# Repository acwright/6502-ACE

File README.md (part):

6502-ACE
========

An **AC6502** retro-style 8-bit computer based on the **65C02** microprocessor.

> 📖 **Guide:** [AC6502 Documentation](https://acwright.github.io/6502-DOCS/) — the user's and programmer's guide for the whole family.
> Start with [Your ACE](https://acwright.github.io/6502-DOCS/your-ace), the tour of this board.

---

**Building one? Every part you need, with supplier numbers and known issues, is in [BOM.md](BOM.md).**

## Table of Contents

- [Overview](#overview)
- [Architecture](#architecture)
- [Systems](#systems)
- [Software](#software)
- [Hardware](#hardware)
  - [ACE Board](#ace-board)
    - [The RTC](#the-rtc)
    - [Known limits](#known-limits)
  - [ACE CF Adapter](#ace-cf-adapter)
  - [ACE RAM Patch](#ace-ram-patch)
- [Which revision to make](#which-revision-to-make)
- [Works with the stock BIOS](#works-with-the-stock-bios)
- [Firmware](#firmware)
  - [Video card](#video-card)
  - [AB Controller](#ab-controller)
  - [ASDA Controller](#asda-controller)
- [CAD](#cad)
- [Production](#production)
- [Schematics](#schematics)
- [Shared lines](#shared-lines)
- [Extra pins: `EXP0`–`EXP3` and `HRDB`](#extra-pins-exp0exp3-and-hrdb)
- [Jumpers](#jumpers)
- [Off-board headers](#off-board-headers)
- [Docs](#docs)
- [Checking the schematics](#checking-the-schematics)
- [Checking the banked RAM](#checking-the-banked-ram)
- [Libraries](#libraries)
- [Bill of Materials](#bill-of-materials)
- [License](#license)

---

## Overview

The AC6502 ecosystem is a family of open-source, 65C02-based computers sharing a common architecture, memory map, and [BIOS](https://github.com/acwright/6502-BIOS). Each computer in the family is purpose-built for a different use case but runs the same software and firmware.

The **ACE** (All-in-one Computer Experience) is a complete, self-contained 65C02 computer on a single PCB. It integrates everything found across the COB's modular cards — CPU, memory, video, audio, storage, serial, GPIO, RTC, and keyboard controller — onto one board, delivering the full experience without a backplane or expansion cards.

## Architecture

All AC6502 computers share:

- **CPU**: 65C02 (or accurate emulation)
- **Memory**: 32KB RAM + 32KB ROM, with optional banked RAM expansion
- **Memory Map**: Standardized across the ecosystem — zero page, stack, I/O space ($8000–$9FFF), system ROM, and interrupt vectors at $FFFA–$FFFF
- **Bus**: 16-bit address bus, 8-bit bidirectional data bus, standard 65C02 control signals (RW, PHI2, RESET, IRQ, NMI, RDY, SYNC)
- **BIOS**: A common [BIOS](https://github.com/acwright/6502-BIOS) provides the kernel, monitor, and BASIC interpreter across all systems

## Systems

| Project | Description |
|---------|-------------|
| [6502-ACE](https://github.com/acwright/6502-ACE) | All-in-one Computer Experience — A single board computer (YOU ARE HERE) |
| [6502-COB](https://github.com/acwright/6502-COB) | Computer On a Backplane — Modular desktop computer with expandable card slots |
| [6502-DEV](https://github.com/acwright/6502-DEV) | Development Environment Vehicle — Emulation-based dev system |
| [6502-KIM](https://github.com/acwright/6502-KIM) | Keypad Input Monitor - KIM-1 inspired minimal computer |
| [6502-VCS](https://github.com/acwright/6502-VCS) | Video Computer System — Cartridge-based retro gaming console |

## Software

| Project | Description |
|---------|-------------|
| [6502-BIOS](https://github.com/acwright/6502-BIOS) | The shared BIOS (kernel, monitor, BASIC) for all AC6502 computers |
| [6502-PICOVDP](https://github.com/acwright/6502-PICOVDP) | Firmware for the ACE's video card, on a PICO9918 PRO v2.0 |
| [6502-EMULATOR](https://github.com/acwright/6502-EMULATOR) | Emulator for the whole family — desktop app, browser build, and a command line for scripted runs |
| [6502-PRG](https://github.com/acwright/6502-PRG) | Template project for writing assembly language programs |
| [6502-CRT](https://github.com/acwright/6502-CRT) | Template project for writing assembly language cartridges |
| [6502-ASM](https://github.com/acwright/6502-ASM) | Assembly language example programs and demos |
| [6502-BAS](https://github.com/acwright/6502-BAS) | BASIC program listings |
| [6502-WOZMON](https://github.com/acwright/6502-WOZMON) | Wozmon as a standalone ROM |
| [6502-NOP](https://github.com/acwright/6502-NOP) | An all-NOP ROM, for probing a board during bring-up |
| [6502-DOCS](https://github.com/acwright/6502-DOCS) | The documentation site — the guide, the printable reference cards, branding and label artwork |
| [cffs](https://github.com/acwright/cffs) | Builds CompactFlash disk images for the BIOS filesystem |
| [bastok](https://github.com/acwright/bastok) | Tokenizes BASIC listings into `.prg` images, and back |
| [bin2woz](https://github.com/acwright/bin2woz) | Converts a binary into a Wozmon serial upload |

## Hardware

This repository contains KiCad 7.0+ PCB designs for the ACE board.

### ACE Board
`Hardware/ACE Board/`

The single integrated board hosting the W65C02S CPU and all peripherals. Provides:

- **CPU**: W65C02S running at 1 MHz
- **RAM**: 32KB SRAM (62256) + Optional 512K banked SRAM (AS6C4008)
- **ROM**: 32KB EEPROM (28C256)
- **Video**: PICO9918 PRO v2.0 running [6502-PICOVDP](https://github.com/acwright/6502-PICOVDP) (VGA 640×480); see [Video card](#video-card). The silkscreen and the BOM's value field say `Pico9918A`
- **Audio**: ARMSID SID chip emulator (3-voice synthesis, RCA output)
- **Storage**: Storage adapter socket
- **Serial**: R6551AP ACIA with MAX238 level shifter (RS-232 via DB9, 50–19200 baud). Male DB-9 wired
  as **DTE**, like a PC, so reaching a laptop needs a **null-modem** cable. `RTS`, `DTR` and `DSR`
  always reach the cable; the `CTS EN` and `DCD EN` jumpers (J2 and J4) pick ground or the cable for
  those two inputs — **both default to ground**
- **GPIO**: 65C22 VIA (20 GPIO pins, 2× 16-bit timers, shift register)
- **RTC**: DS1511Y real-time clock with battery-backed NVRAM. Any revision also takes the RTC Adapter, and Rev 1.1 a DS1501; see [The RTC](#the-rtc)
- **Keyboard Controller**: ATmega1284 running AB Controller firmware
- **Input**: PS/2 keyboard connector and 8×8 keyboard matrix header
- **Joystick**: Two Atari 2600-compatible joystick ports (JOYSTICK A on VIA PORT A and JOYSTICK B on VIA PORT B, `J6` and `J8`), read as `JOY(2)` and `JOY(1)` respectively
- **Clock**: 16 MHz DIP-14 full can oscillator (X1); drives the ATmega1284 at 16 MHz and, through the 74HC163 divider (U5), the 65C02, VIA, ACIA and SID at 1 MHz, the speed every AC6502 is tested at. The PHI2 SELECT jumper (J1) offers 2 MHz on pins 2 and 3.
  - **Rev 1.0: keep J1 on 1 MHz** (pins 1 and 2). Its SID is clocked from the 1 MHz output whatever J1 says, so at 2 MHz it answers only every other CPU cycle.
  - **Rev 1.1: 2 MHz is an option at the builder's risk.** The CPU, VIA, ACIA and SID all follow J1. The limit the 2 MHz tests found, on 2026-11-11, is the RAM at U7: an Alliance AS6C62256 there misread at 2 MHz with one lot of 74HC00 at U14, the gate that makes `RB` and `WB`, and the Hitachi HM62256LP-70 read clean with the same 74HC00. The parts list orders the Hitachi for both revisions (2026-11-28), with a 74HC00 at U14. The cause of the Alliance's misreads isn't known. A made Rev 1.0 with an Alliance can misread at 1 MHz too: see the RAM row in [BOM.md's Known issues](BOM.md#known-issues). The R6551AP is rated for 2 MHz, with no margin, and read back clean at that speed. BIOS 2.1.0 finds the CompactFlash card at boot at 2 MHz, and reads and writes it clean there (tested on Rev 1.0 with the 74HCT00 at U14, 2026-11-12); BIOS 2.0.x misses the card at boot at 2 MHz.

**The serial handshake jumpers.** `CTS EN` and `DCD EN` (J2 and J4) both default to **ground**, and
that is how the boards were built. Ground means the line is permanently asserted, so the ACIA can
always send and always receive. Moved to the cable, they do real work — measured on a real R6551 in
2026: `CTS` high stops the transmitter dead and `DCD` high stops the receiver, losing the byte that
arrives. A board jumpered to the cable and plugged into something that does not assert those lines
shows no banner and no echo at all, and looks broken when it is not.
- **Reset**: Manual reset button (SW70, just above <kbd>Esc</kbd>) connected to the ATmega1284, which also provides power-on reset to the 65C02
- **Power**: 5V DC via barrel jack, center-positive only. The jack goes straight to the power switch, so `VCC` gets the full 5 V, and nothing protects the board from a reversed supply

**Cards on `CART` and `BUS`.** `IRQB`, `NMIB` and `RESB` are shared by several devices on the board and by
anything plugged into `CART` and `BUS` (J17 and J18). A card may only pull
those lines low, open-drain, and must never drive them high: a device that drives a shared line high holds it
there against every other device that pulls it low. A video card built around a pico9918 has the same `/INT`
problem as U3, and needs the same diode on the card.

#### The RTC

U18 is the real-time clock, with 256 bytes of battery-backed NVRAM. The DS1511Y is a DS1501 with its 32.768 kHz
crystal and a lithium cell built into one module: the same registers and pinout, so the BIOS runs either. The
[RTC Adapter](https://github.com/acwright/6502-COB#adapters), in 6502-COB, is a DS1501 and its crystal on a plug that fits any revision's socket, for less. Rev 1.1
also puts the crystal on the board (`Y2`), so its socket takes the bare chip too:

| Rev | DS1511Y | RTC Adapter | DS1501 (DIP) |
|---|---|---|---|
| 1.0 | Yes, the part it was made and tested with | Yes, untested | No: it has no crystal |
| 1.1 | Yes | Yes, untested | Yes, untested |

With the RTC Adapter or a DS1501:
- **Keep the CR2032 fitted** (`BT1`). It is the DS1501's only backup, so taking it out loses the time and the NVRAM.
  A DS1511Y has its own cell as well.
- **Use BIOS 1.8 or 2.2.0 or later.** A new DS1501 may start with its Crystal Select bit set, and then it runs slow
  on the 6 pF crystal; the BIOS clears the bit at every boot from those releases on
  ([6502-BIOS #4](https://github.com/acwright/6502-BIOS/issues/4)).
- **The DS1501YN+, the DIP chip, is not for new designs** (NRND). Digi-Key lists it (2026-11-20); Mouser doesn't. The
  RTC Adapter's DS1501YZN+, in SOIC, is active.

#### Known limits

- **The SID probe:** BIOS 2.0.x missed the SID (an ARMSID) at 1 MHz about once in a dozen boots, because it read voice 3 only once. BIOS 2.1.0 reads it several times: on 2026-11-12 it found the ARMSID on 10 boots of 10, and with IO7 switched off on IO ENABLE (SW69) found no SID on 10 of 10. Use 2.1.0 or later.
- **The CompactFlash probe:** BIOS 2.0.x waited for the card with a loop counted in CPU cycles, about 851 ms at 1 MHz and half that at 2 MHz, so a slow card could be missed. BIOS 2.1.0 passes over an empty slot at once and otherwise waits up to 3.0 s at 1 MHz (1.5 s at 2 MHz). A Promaster 128 MB card is ready in about 434 ms.

### ACE CF Adapter
`Hardware/ACE CF Adapter/`

A CompactFlash adapter board that connects to the Storage header on the ACE Board. Provides:

- **Interface**: 8-bit IDE (True IDE) mode
- **Storage**: CompactFlash socket. The BIOS filesystem divides the card into 256 disk banks of 1 MB each, so 256 MB is the usable capacity regardless of the card fitted
- **Revisions**: Rev 1.0 is the board on sale, and its silkscreen says `J21` for STORAGE and `J3` for the CF socket. See the [revision history](REVISIONS.md#ace-cf-adapter)

### ACE RAM Patch
`Hardware/ACE RAM Patch/`

A patch board for Rev 1.0 of the ACE Board that corrects the extended RAM (banked SRAM) decoding, with the same logic as Rev 1.1. U12 and U13 come off the ACE, chips and sockets, and the patch is soldered underneath in their place. Provides:

- **Fix**: `LOADL` and `LOADH` go high only on a write to the bank register, `$83FF` or `$87FF`, while PHI2 is high. Rev 1.0 pulsed both latches whenever the bus was idle, and the first patch (Rev 1.0) fixed that but still loaded a latch on any write to `$8300`–`$83FE` and `$80FF`–`$82FF` (and the same in the `$8400` window)
- **Interface**: two DIP-14 footprints of pin headers, J1 into U12's holes and J2 into U13's, soldered on both boards. The patch mounts front side up under the ACE, so its layout is not mirrored; U13's pin 1 is 23.00 mm from U12's pin 1 along the row
- **Layout**: U1, J1, J2 and U2 in one row, 92.6 × 13.1 mm. J1 and J2 are on the front, facing the ACE; U1 (74HC00) and U2 (74HC02) are on the back, hanging below, so trim their leads flush on the front. The patch hangs about 8.5 mm below the ACE: the header, the board, and the chips
- **Rev 1.1**: replaces the Rev 1.0 patch, which plugged into U13 alone
- **Status**: Rev 1.1 is verified on hardware. Its decode passes `Tests/check-schematics.mjs`, and on 2026-11-03 an ACE Board Rev 1.0 with the patch fitted passed `node Tests/check-ram.mjs --expect FF` with every card in place: `HW_PRESENT` read `$FF` after each of 10 restarts, each latch loaded only on its own address, and every bank of both windows held its own patterns, with 0 failures in 3 runs. The same board had 0 failures in 3 runs without the video card and the CF Adapter, reading `$77`. Without the patch, a Rev 1.0 reads `$FD`, because the BIOS doesn't find the `$8400` window. See [Checking the banked RAM](#checking-the-banked-ram)

<!-- Which revision to make: generated by Tools/revision-audit/register.py from Tools/data/orders.json. Edit that file, not this section. -->
## Which revision to make

**Make the newest revision of a board, and check its label first.** The table below gives each board's newest revision. A newer revision fixes what was found on the older ones. Every revision, old and new, is in [REVISIONS.md](REVISIONS.md), with what changed in each.

Each revision carries one of three labels:

- **Tested:** This revision was built and tested.
- **Proven design:** Not built at this revision, but its circuit is proven. Either it is a tested revision's circuit, or each change copies a circuit built and tested on another board or on the bench, or is a textbook circuit that leaves everything the tested revision does as it was. Any other change is silkscreen text, part values, mounting holes, outline clean-up, parts moved a fraction of a millimetre onto their grid, capacitor pitch, socket outlines, a footprint swap with the same holes, a solder jumper's default, the solder mask or paste at a card edge, or tracks rerouted or pours refilled with DRC and the netlist check passing. A builder can treat it as tested.
- **Untested:** The circuit, the power path or the layout changed in a way that only a built board proves, or the board has never been built at all.

[BOM.md](BOM.md) has the parts for every revision, and its known issues.

| Board | Newest revision | Label | Why |
|---|---|---|---|
| ACE Board | 1.1 | **Proven design** | Each change is a circuit already tested on a Rev 1.0: the ACE RAM Patch 1.1's bank-latch decode and the video card's `/INT` diode, both run on the bench, and the ACIA's crystal jumpers, which ship open. The audio jack's pins are put right, `SOB` is tied high, the pull-ups are 10k, and the tracks are rerouted, with the decode check passing. The DS1501 option at U18, with its crystal `Y2`, is untested, and so are the 10k pull-ups on the PS/2 lines, a textbook circuit. |
| ACE CF Adapter | 1.1 | **Proven design** | The same circuit as the tested Rev 1.0, renumbered and in surface-mount parts for JLCPCB assembly. The new LCSC socket fits the same footprint, but no board has been built with it yet. |
| ACE RAM Patch | 1.1 | **Tested** | Built and tested on an ACE Board Rev 1.0, 2026-11-03. |
| ACE SD Adapter Bottom | 1.1 | **Untested** | A new board: an SD card the stock BIOS takes for CompactFlash, with a built-in drive; the ACE SD Adapter Top, stacked on it, carries the SD card socket. Not yet made. |
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
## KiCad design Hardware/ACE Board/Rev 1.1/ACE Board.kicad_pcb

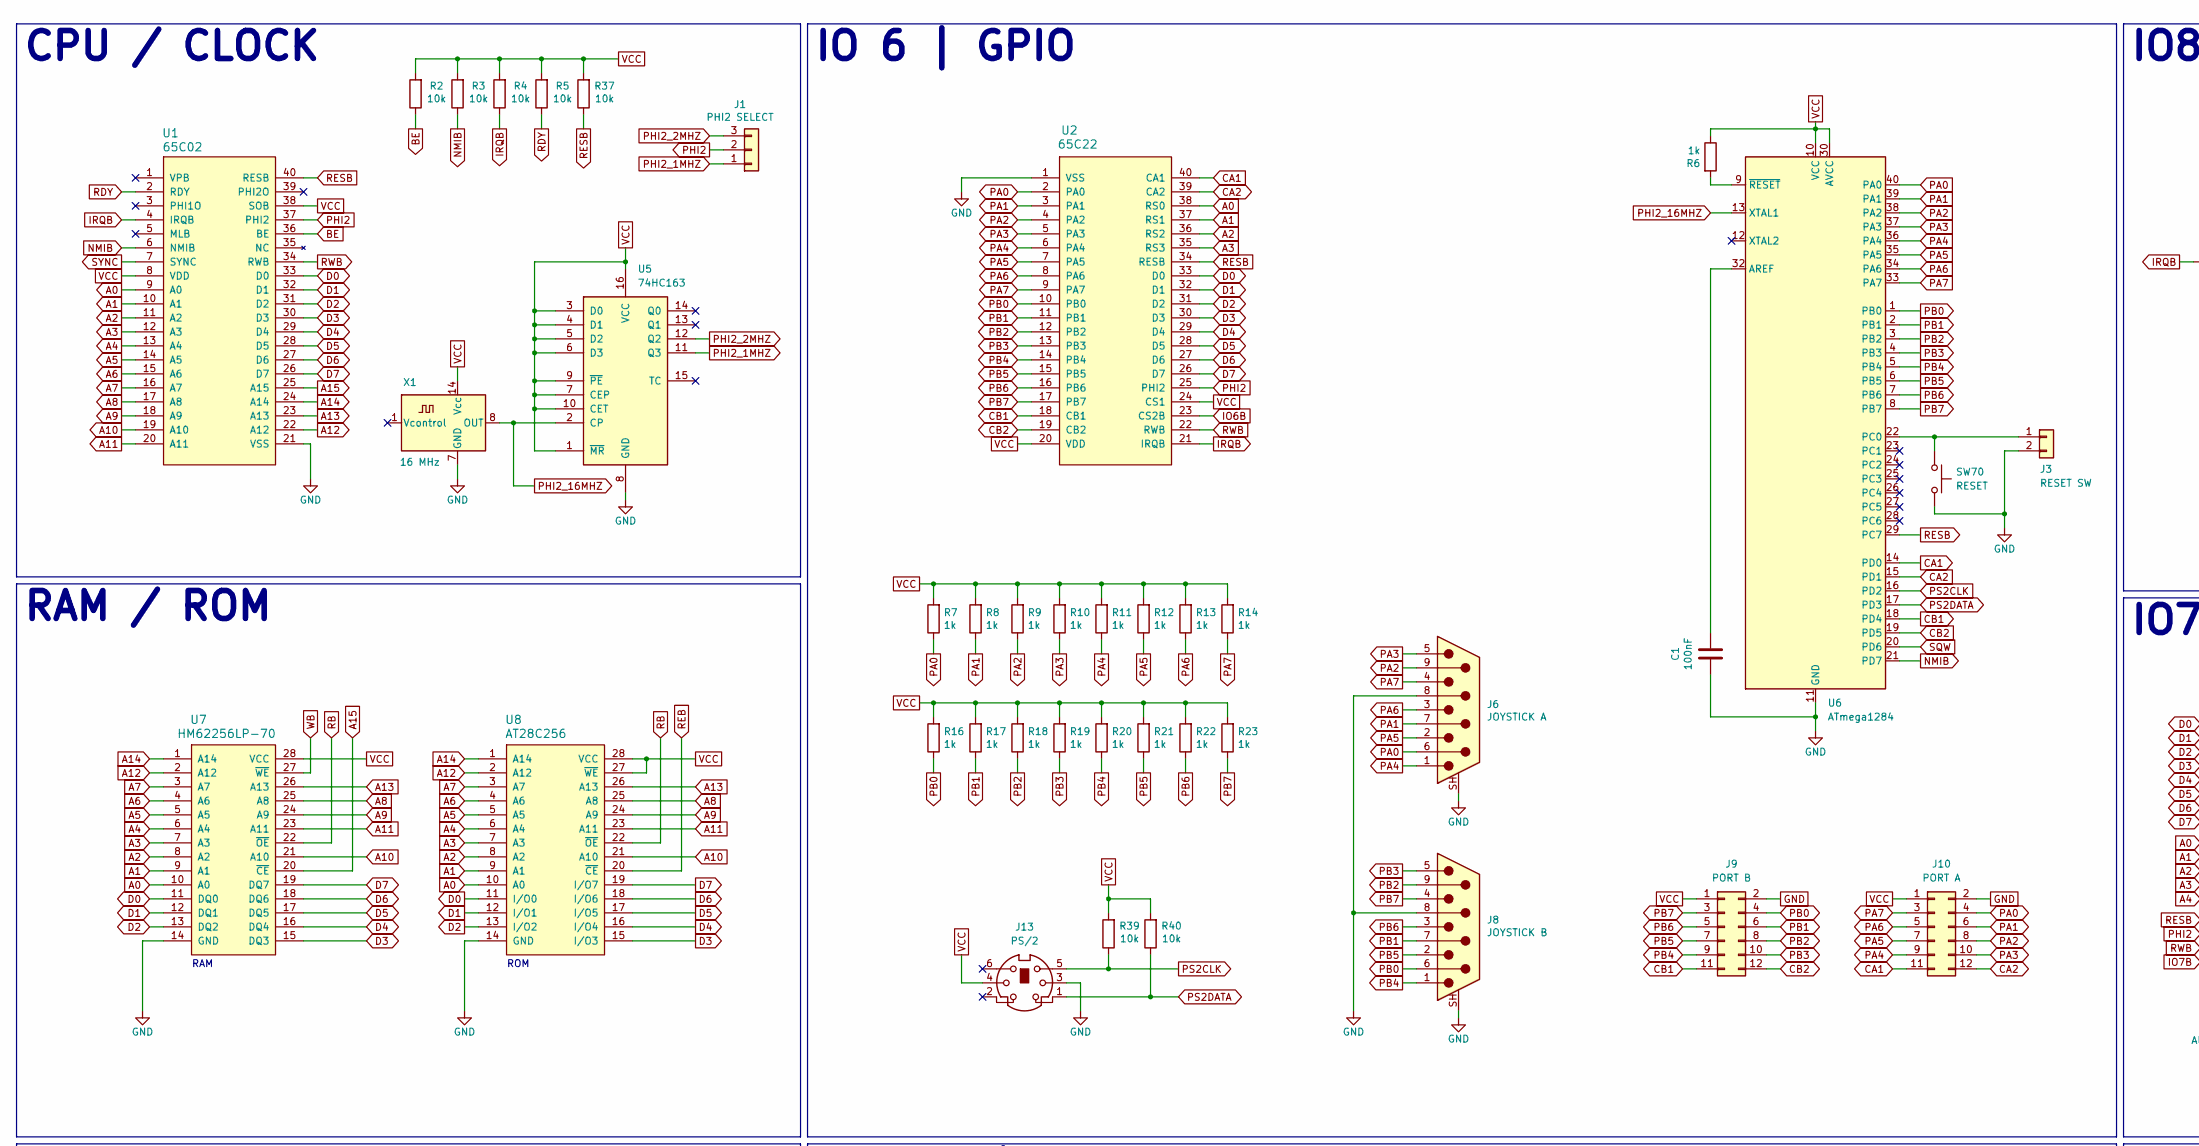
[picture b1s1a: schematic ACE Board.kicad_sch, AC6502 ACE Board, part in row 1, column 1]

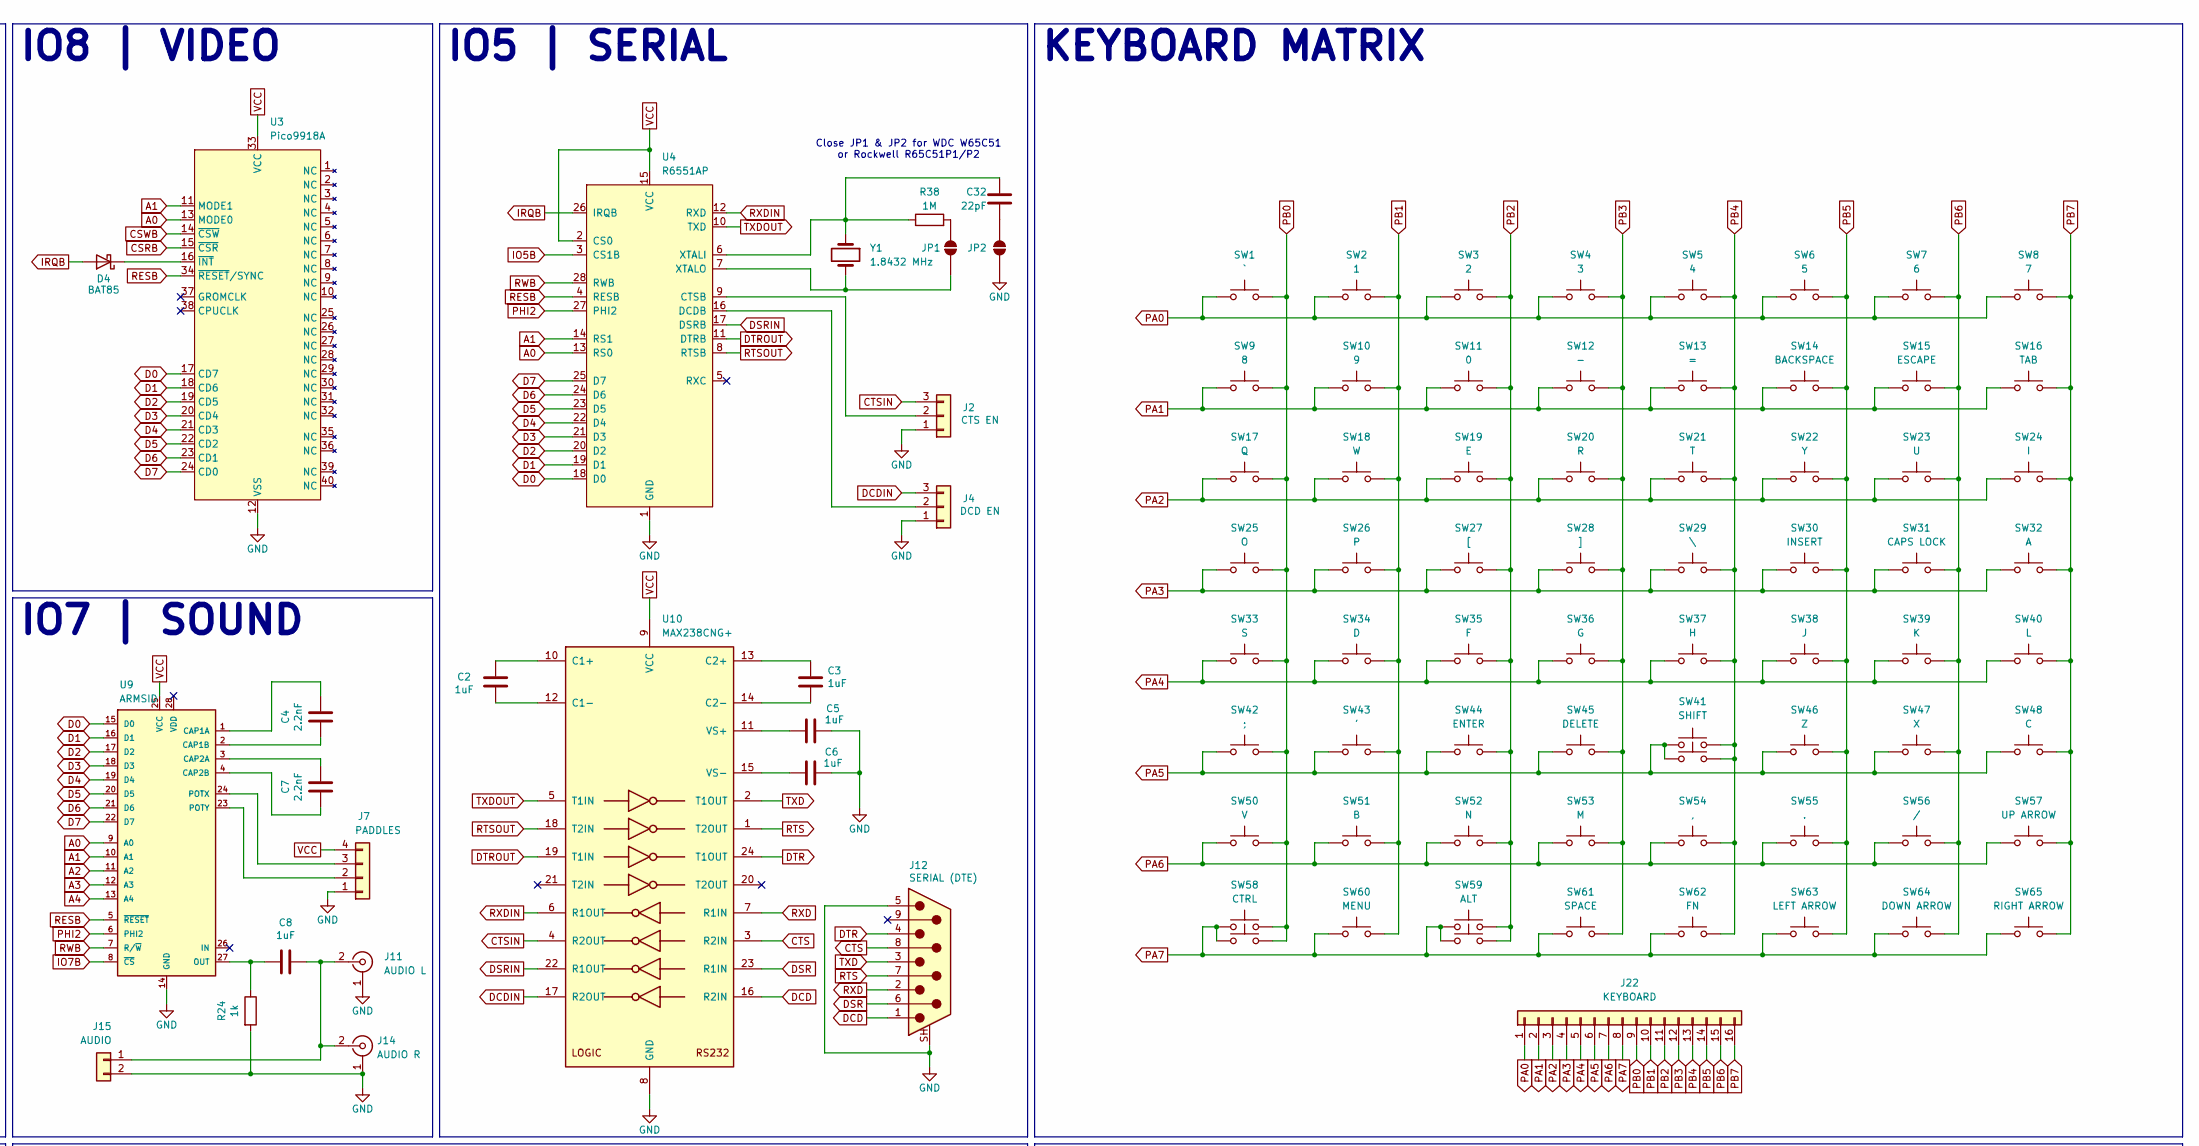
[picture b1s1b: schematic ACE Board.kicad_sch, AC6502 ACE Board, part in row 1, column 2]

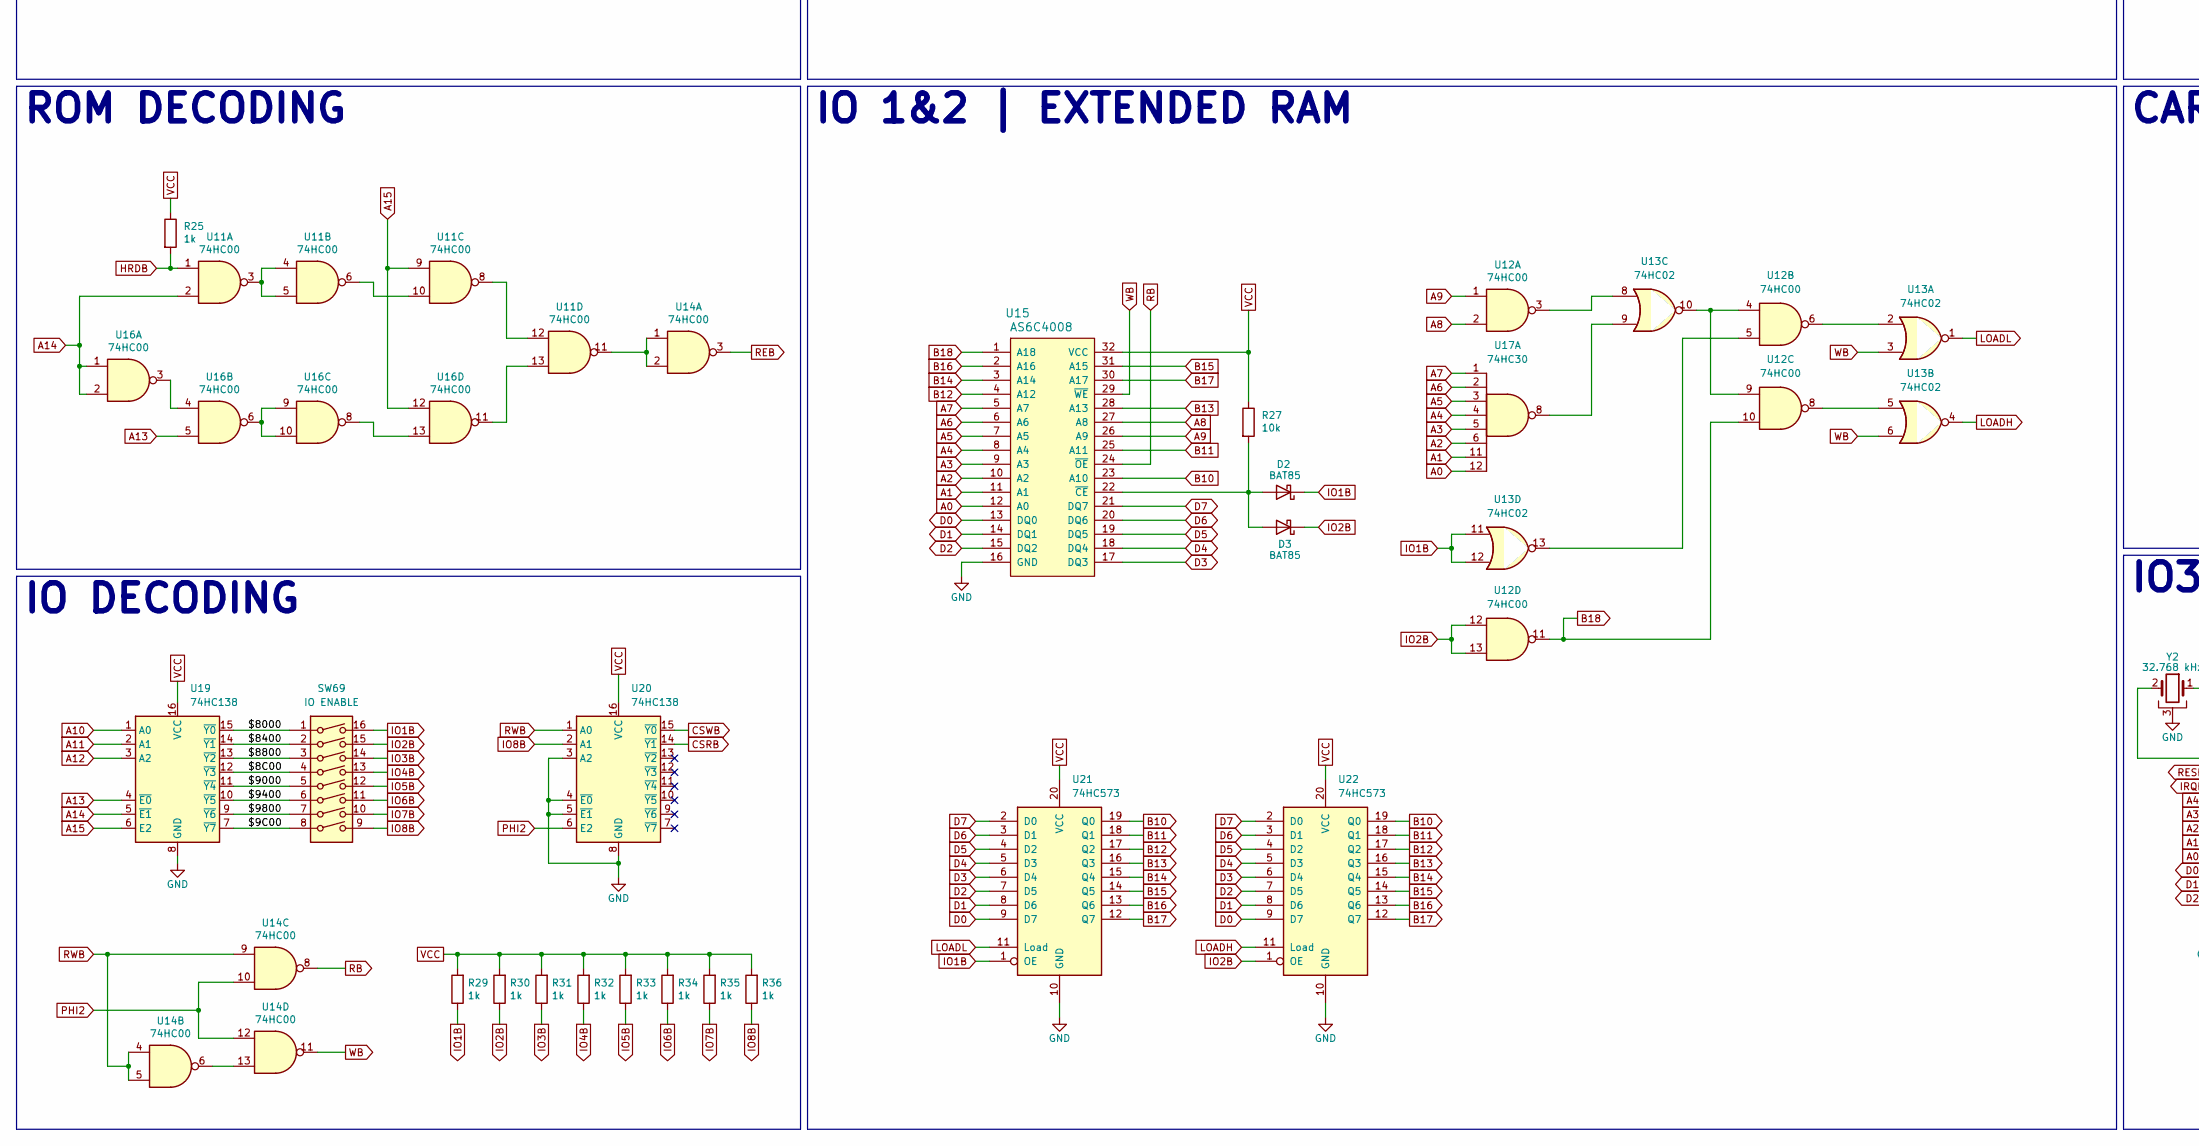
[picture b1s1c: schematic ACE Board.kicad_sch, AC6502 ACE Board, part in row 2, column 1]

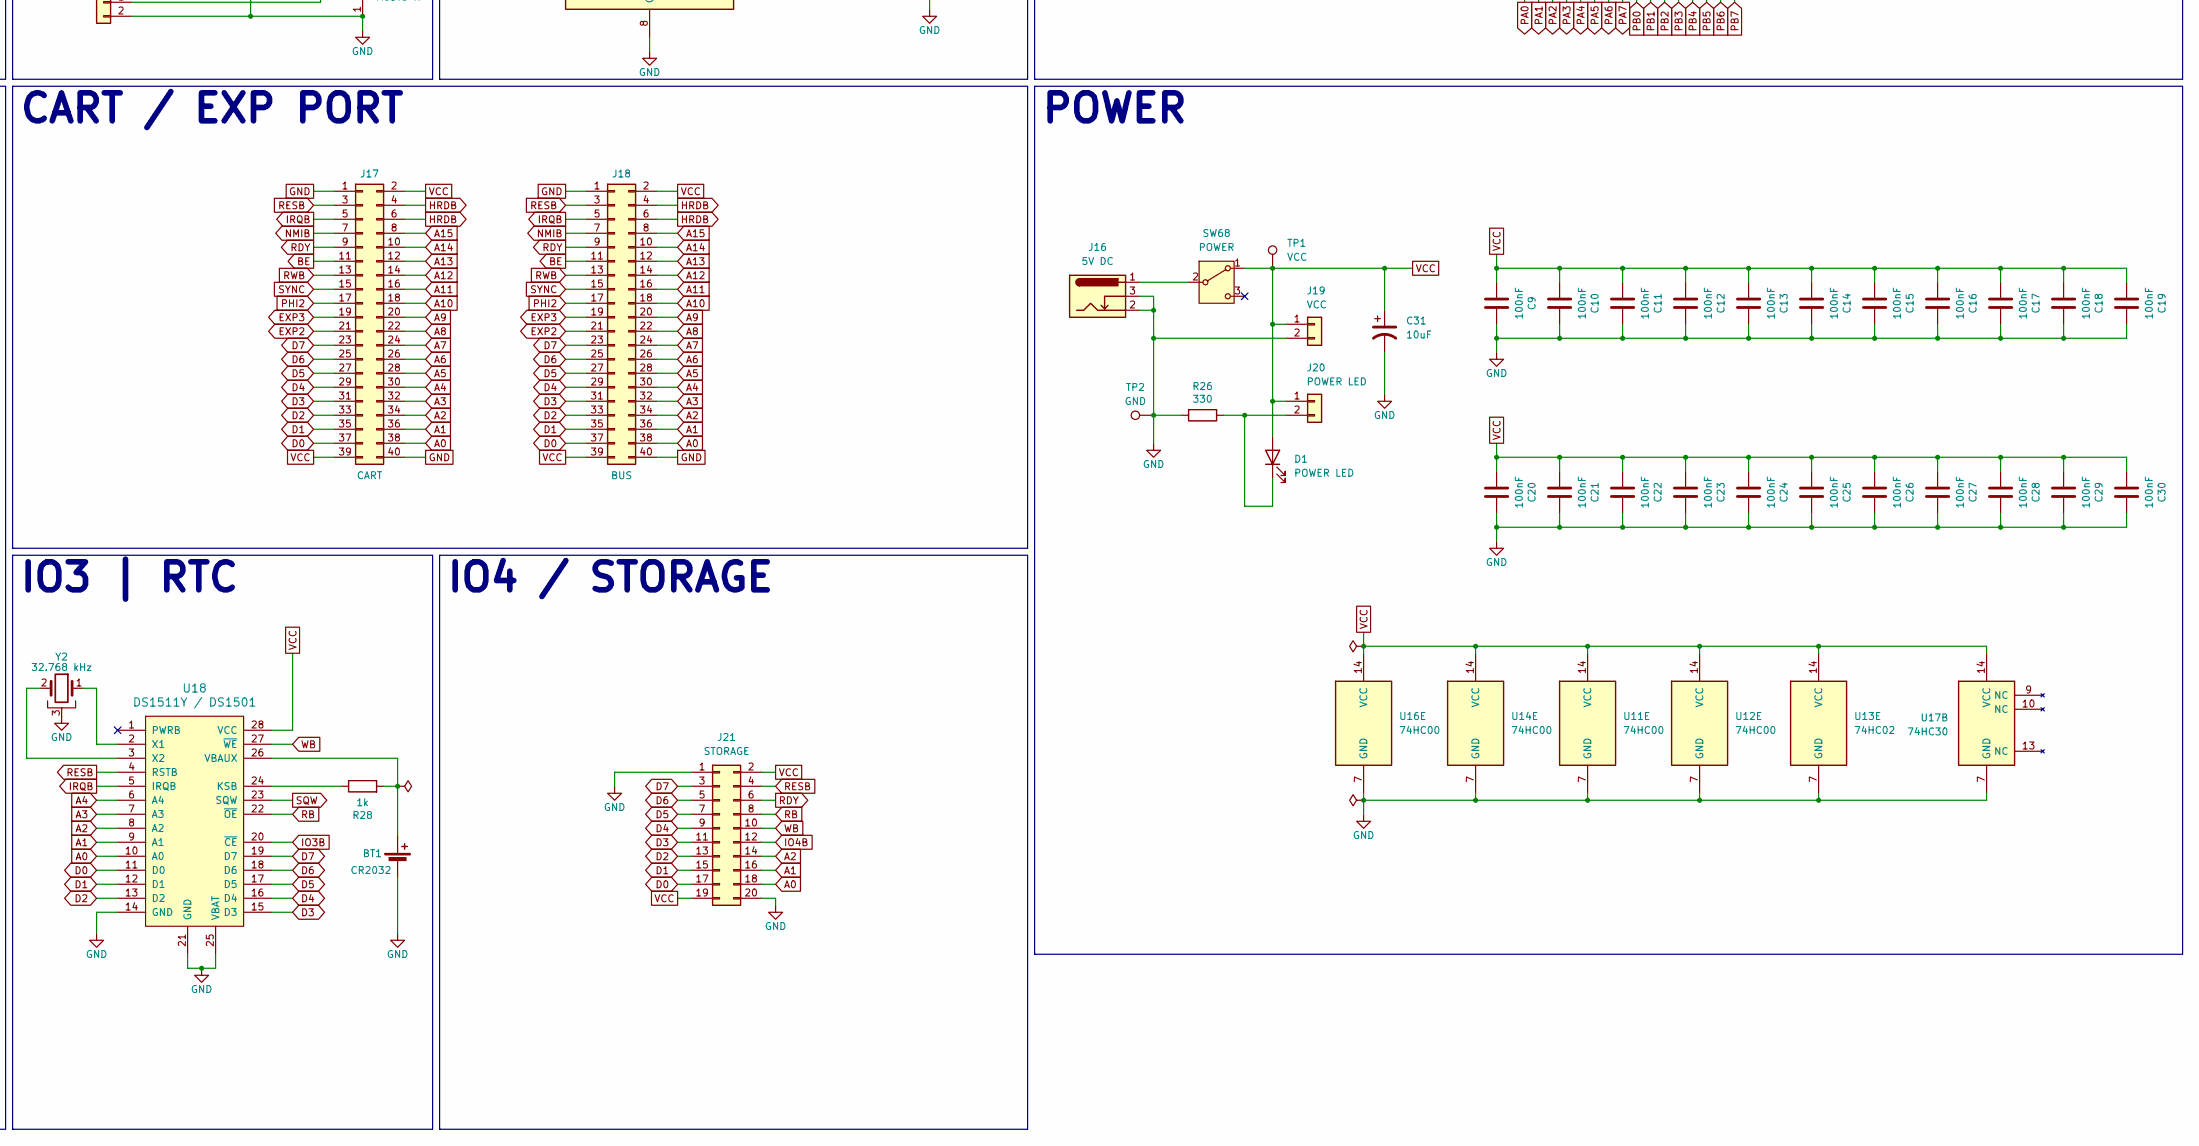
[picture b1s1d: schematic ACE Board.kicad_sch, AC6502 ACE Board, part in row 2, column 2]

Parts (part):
BT1: CR2032; CR2032 Holder Numbered; Digikey 343-BAT-HLD-001-THM-TRCT-ND
C1, C9, C10, C11, C12, C13, C14, C15, C16, C17, C18, C19, C20, C21, C22, C23, C24, C25, C26, C27, C28, C29, C30: 100nF; C_Disc_D5.0mm_W2.5mm_P2.50mm; Digikey 478-3187-ND
C2, C3, C5, C6, C8: 1uF; C_Disc_D5.0mm_W2.5mm_P2.50mm; Digikey 478-7667-ND
C4, C7: 2.2nF; C_Disc_D5.0mm_W2.5mm_P2.50mm; Digikey 478-11698-ND
C31: 10uF; CP_Radial_D4.0mm_P1.50mm; Digikey P14482-ND
C32: 22pF; C_Disc_D5.0mm_W2.5mm_P2.50mm; Digikey 478-4846-ND
D1: POWER LED; LED_D3.0mm; Digikey 732-5008-ND
D2, D3, D4: BAT85; D_DO-35_SOD27_P7.62mm_Horizontal; Digikey BAT85SCT-ND
J1: PHI2 SELECT; PinHeader_1x03_P2.54mm_Vertical; Digikey S1011EC-40-ND
J2: CTS EN; PinHeader_1x03_P2.54mm_Vertical; Digikey S1011EC-40-ND
J3: RESET SW; PinHeader_1x02_P2.54mm_Vertical; Digikey S1011EC-40-ND
J4: DCD EN; PinHeader_1x03_P2.54mm_Vertical; Digikey S1011EC-40-ND
J6: JOYSTICK A; DSUB-9_Pins_Horizontal_P2.77x2.84mm_EdgePinOffset7.70mm_Hou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; Digikey 609-1481-ND
J7: PADDLES; PinHeader_1x04_P2.54mm_Vertical; Digikey S1011EC-40-ND
J8: JOYSTICK B; DSUB-9_Pins_Horizontal_P2.77x2.84mm_EdgePinOffset7.70mm_Hou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; Digikey 609-1481-ND
J9: PORT B; 6502 GPIO Connector; Digikey 2057-BHR-12-VUA-ND
J10: PORT A; 6502 GPIO Connector; Digikey 2057-BHR-12-VUA-ND
J11: AUDIO L; RCA Jack White; Digikey PJRAN1X1U02X-ND
J12: SERIAL (DTE); DSUB-9_Pins_Horizontal_P2.77x2.84mm_EdgePinOffset7.70mm_Hou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; Digikey 609-1481-ND
J13: PS/2; PS2 Jack; Mouser 806-KMDGX-6S-BS
J14: AUDIO R; RCA Jack White; Digikey PJRAN1X1U03X-ND
J15: AUDIO; PinHeader_1x02_P2.54mm_Vertical; Digikey S1011EC-40-ND
J16: 5V DC; BarrelJack_Horizontal; Digikey CP-102AH-ND
J17: CART; 6502 Card Slot; Digikey A31723-ND
J18: BUS; 6502 Bus Connector; Digikey 732-5401-ND
J19: VCC; PinHeader_1x02_P2.54mm_Vertical; Digikey S1011EC-40-ND
J20: POWER LED; PinHeader_1x02_P2.54mm_Vertical; Digikey S1011EC-40-ND
J21: STORAGE; PinSocket_2x10_P2.54mm_Horizontal; Digikey S5563-ND
J22: KEYBOARD; PinHeader_1x16_P2.00mm_Vertical; Digikey 2057-2PH1-16-UA-ND
JP1, JP2: SolderJumper_2_Open; SolderJumper-2_P1.3mm_Open_RoundedPad1.0x1.5mm
R2, R3, R4, R5, R27, R37, R39, R40: 10k; R_Axial_DIN0204_L3.6mm_D1.6mm_P5.08mm_Horizontal; Digikey 13-MFR-12FTF52-10KCT-ND
R6, R7, R8, R9, R10, R11, R12, R13, R14, R16, R17, R18, R19, R20, R21, R22, R23, R24, R25, R28, R29, R30, R31, R32, R33, R34, R35, R36: 1k; R_Axial_DIN0204_L3.6mm_D1.6mm_P5.08mm_Horizontal; Digikey 13-MFR-12FTF52-1KCT-ND
R26: 330; R_Axial_DIN0204_L3.6mm_D1.6mm_P5.08mm_Horizontal; Digikey 13-MFR-12FTF52-330RCT-ND
R38: 1M; R_Axial_DIN0204_L3.6mm_D1.6mm_P5.08mm_Horizontal; Digikey 13-MFR-12FTF52-1MCT-ND
SW1: `; SW_Cherry_MX_1.00u_PCB; Digikey 1644-MX2A-E1NA-ND
SW2: 1; SW_Cherry_MX_1.00u_PCB; Digikey 1644-MX2A-E1NA-ND
SW3: 2; SW_Cherry_MX_1.00u_PCB; Digikey 1644-MX2A-E1NA-ND
SW4: 3; SW_Cherry_MX_1.00u_PCB; Digikey 1644-MX2A-E1NA-ND
SW5: 4; SW_Cherry_MX_1.00u_PCB; Digikey 1644-MX2A-E1NA-ND
SW6: 5; SW_Cherry_MX_1.00u_PCB; Digikey 1644-MX2A-E1NA-ND
SW7: 6; SW_Cherry_MX_1.00u_PCB; Digikey 1644-MX2A-E1NA-ND
SW8: 7; SW_Cherry_MX_1.00u_PCB; Digikey 1644-MX2A-E1NA-ND
SW9: 8; SW_Cherry_MX_1.00u_PCB; Digikey 1644-MX2A-E1NA-ND
SW10: 9; SW_Cherry_MX_1.00u_PCB; Digikey 1644-MX2A-E1NA-ND
SW11: 0; SW_Cherry_MX_1.00u_PCB; Digikey 1644-MX2A-E1NA-ND
SW12: -; SW_Cherry_MX_1.00u_PCB; Digikey 1644-MX2A-E1NA-ND
SW13: =; SW_Cherry_MX_1.00u_PCB; Digikey 1644-MX2A-E1NA-ND
SW14: BACKSPACE; SW_Cherry_MX_2.00u_PCB; Digikey 1644-MX2A-E1NA-ND
SW15: ESCAPE; SW_Cherry_MX_1.00u_PCB; Digikey 1644-MX2A-E1NA-ND
SW16: TAB; SW_Cherry_MX_1.50u_PCB; Digikey 1644-MX2A-E1NA-ND
SW17: Q; SW_Cherry_MX_1.00u_PCB; Digikey 1644-MX2A-E1NA-ND
SW18: W; SW_Cherry_MX_1.00u_PCB; Digikey 1644-MX2A-E1NA-ND
SW19: E; SW_Cherry_MX_1.00u_PCB; Digikey 1644-MX2A-E1NA-ND
SW20: R; SW_Cherry_MX_1.00u_PCB; Digikey 1644-MX2A-E1NA-ND
SW21: T; SW_Cherry_MX_1.00u_PCB; Digikey 1644-MX2A-E1NA-ND
SW22: Y; SW_Cherry_MX_1.00u_PCB; Digikey 1644-MX2A-E1NA-ND
SW23: U; SW_Cherry_MX_1.00u_PCB; Digikey 1644-MX2A-E1NA-ND
SW24: I; SW_Cherry_MX_1.00u_PCB; Digikey 1644-MX2A-E1NA-ND
SW25: O; SW_Cherry_MX_1.00u_PCB; Digikey 1644-MX2A-E1NA-ND
SW26: P; SW_Cherry_MX_1.00u_PCB; Digikey 1644-MX2A-E1NA-ND
SW27: [; SW_Cherry_MX_1.00u_PCB; Digikey 1644-MX2A-E1NA-ND
SW28: ]; SW_Cherry_MX_1.00u_PCB; Digikey 1644-MX2A-E1NA-ND
SW29: \; SW_Cherry_MX_1.50u_PCB; Digikey 1644-MX2A-E1NA-ND
SW30: INSERT; SW_Cherry_MX_1.00u_PCB; Digikey 1644-MX2A-E1NA-ND
SW31: CAPS LOCK; SW_Cherry_MX_1.75u_PCB; Digikey 1644-MX2A-E1NA-ND
SW32: A; SW_Cherry_MX_1.00u_PCB; Digikey 1644-MX2A-E1NA-ND
SW33: S; SW_Cherry_MX_1.00u_PCB; Digikey 1644-MX2A-E1NA-ND
SW34: D; SW_Cherry_MX_1.00u_PCB; Digikey 1644-MX2A-E1NA-ND
SW35: F; SW_Cherry_MX_1.00u_PCB; Digikey 1644-MX2A-E1NA-ND
SW36: G; SW_Cherry_MX_1.00u_PCB; Digikey 1644-MX2A-E1NA-ND
SW37: H; SW_Cherry_MX_1.00u_PCB; Digikey 1644-MX2A-E1NA-ND
SW38: J; SW_Cherry_MX_1.00u_PCB; Digikey 1644-MX2A-E1NA-ND
SW39: K; SW_Cherry_MX_1.00u_PCB; Digikey 1644-MX2A-E1NA-ND
SW40: L; SW_Cherry_MX_1.00u_PCB; Digikey 1644-MX2A-E1NA-ND
SW41, SW49: SHIFT; SW_Cherry_MX_2.25u_PCB; Digikey 1644-MX2A-E1NA-ND
SW42: ;; SW_Cherry_MX_1.00u_PCB; Digikey 1644-MX2A-E1NA-ND
SW43: '; SW_Cherry_MX_1.00u_PCB; Digikey 1644-MX2A-E1NA-ND
SW44: ENTER; SW_Cherry_MX_2.25u_PCB; Digikey 1644-MX2A-E1NA-ND
SW45: DELETE; SW_Cherry_MX_1.00u_PCB; Digikey 1644-MX2A-E1NA-ND
SW46: Z; SW_Cherry_MX_1.00u_PCB; Digikey 1644-MX2A-E1NA-ND
SW47: X; SW_Cherry_MX_1.00u_PCB; Digikey 1644-MX2A-E1NA-ND
SW48: C; SW_Cherry_MX_1.00u_PCB; Digikey 1644-MX2A-E1NA-ND
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
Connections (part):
/$8C00: SW69.4, U19.12 (~Y3)
/$9C00: SW69.8, U19.7 (~Y7)
/$8000: SW69.1, U19.15 (~Y0)
/$8400: SW69.2, U19.14 (~Y1)
/$8800: SW69.3, U19.13 (~Y2)
/$9000: SW69.5, U19.11 (~Y4)
/$9400: SW69.6, U19.10 (~Y5)
/$9800: SW69.7, U19.9 (~Y6)
A0: J17.38, J18.38, J21.18, U1.9 (A0), U2.38 (RS0), U3.13 (MODE0), U4.13 (RS0), U7.10 (A0), U8.10 (A0), U9.9 (A0), U15.12 (A0), U17.12, U18.10 (A0)
A1: J17.36, J18.36, J21.16, U1.10 (A1), U2.37 (RS1), U3.11 (MODE1), U4.14 (RS1), U7.9 (A1), U8.9 (A1), U9.10 (A1), U15.11 (A1), U17.11, U18.9 (A1)
A2: J17.34, J18.34, J21.14, U1.11 (A2), U2.36 (RS2), U7.8 (A2), U8.8 (A2), U9.11 (A2), U15.10 (A2), U17.6, U18.8 (A2)
A3: J17.32, J18.32, U1.12 (A3), U2.35 (RS3), U7.7 (A3), U8.7 (A3), U9.12 (A3), U15.9 (A3), U17.5, U18.7 (A3)
A4: J17.30, J18.30, U1.13 (A4), U7.6 (A4), U8.6 (A4), U9.13 (A4), U15.8 (A4), U17.4, U18.6 (A4)
A5: J17.28, J18.28, U1.14 (A5), U7.5 (A5), U8.5 (A5), U15.7 (A5), U17.3
A6: J17.26, J18.26, U1.15 (A6), U7.4 (A6), U8.4 (A6), U15.6 (A6), U17.2
A7: J17.24, J18.24, U1.16 (A7), U7.3 (A7), U8.3 (A7), U15.5 (A7), U17.1
A8: J17.22, J18.22, U1.17 (A8), U7.25 (A8), U8.25 (A8), U12.2, U15.27 (A8)
A9: J17.20, J18.20, U1.18 (A9), U7.24 (A9), U8.24 (A9), U12.1, U15.26 (A9)
A10: J17.18, J18.18, U1.19 (A10), U7.21 (A10), U8.21 (A10), U19.1 (A0)
A11: J17.16, J18.16, U1.20 (A11), U7.23 (A11), U8.23 (A11), U19.2 (A1)
A12: J17.14, J18.14, U1.22 (A12), U7.2 (A12), U8.2 (A12), U19.3 (A2)
A13: J17.12, J18.12, U1.23 (A13), U7.26 (A13), U8.26 (A13), U16.5, U19.4 (~E0)
A14: J17.10, J18.10, U1.24 (A14), U7.1 (A14), U8.1 (A14), U11.2, U16.1, U16.2, U19.5 (~E1)
A15: J17.8, J18.8, U1.25 (A15), U7.20 (~CE), U11.9, U16.12, U19.6 (E2)
B10: U15.23 (A10), U21.19 (Q0), U22.19 (Q0)
B11: U15.25 (A11), U21.18 (Q1), U22.18 (Q1)
B12: U15.4 (A12), U21.17 (Q2), U22.17 (Q2)
B13: U15.28 (A13), U21.16 (Q3), U22.16 (Q3)
B14: U15.3 (A14), U21.15 (Q4), U22.15 (Q4)
B15: U15.31 (A15), U21.14 (Q5), U22.14 (Q5)
B16: U15.2 (A16), U21.13 (Q6), U22.13 (Q6)
B17: U15.30 (A17), U21.12 (Q7), U22.12 (Q7)
B18: U12.10, U12.11, U15.1 (A18)
BE: J17.11, J18.11, R2.1, U1.36 (BE)
CA1: J10.11, U2.40 (CA1), U6.14 (PD0)
CA2: J10.12, U2.39 (CA2), U6.15 (PD1)
CB1: J9.11, U2.18 (CB1), U6.18 (PD4)
CB2: J9.12, U2.19 (CB2), U6.19 (PD5)
CSRB: U3.15 (~CSR), U20.14 (~Y1)
CSWB: U3.14 (~CSW), U20.15 (~Y0)
CTS: J12.8, U10.3 (R2IN)
CTSIN: J2.3, U10.4 (R2OUT)
D0: J17.37, J18.37, J21.17, U1.33 (D0), U2.33 (D0), U3.17 (CD7), U4.18 (D0), U7.11 (DQ0), U8.11 (I/O0), U9.15 (D0), U15.13 (DQ0), U18.11 (D0), U21.9 (D7), U22.9 (D7)
D1: J17.35, J18.35, J21.15, U1.32 (D1), U2.32 (D1), U3.18 (CD6), U4.19 (D1), U7.12 (DQ1), U8.12 (I/O1), U9.16 (D1), U15.14 (DQ1), U18.12 (D1), U21.8 (D6), U22.8 (D6)
D2: J17.33, J18.33, J21.13, U1.31 (D2), U2.31 (D2), U3.19 (CD5), U4.20 (D2), U7.13 (DQ2), U8.13 (I/O2), U9.17 (D2), U15.15 (DQ2), U18.13 (D2), U21.7 (D5), U22.7 (D5)
D3: J17.31, J18.31, J21.11, U1.30 (D3), U2.30 (D3), U3.20 (CD4), U4.21 (D3), U7.15 (DQ3), U8.15 (I/O3), U9.18 (D3), U15.17 (DQ3), U18.15 (D3), U21.6 (D4), U22.6 (D4)
D4: J17.29, J18.29, J21.9, U1.29 (D4), U2.29 (D4), U3.21 (CD3), U4.22 (D4), U7.16 (DQ4), U8.16 (I/O4), U9.19 (D4), U15.18 (DQ4), U18.16 (D4), U21.5 (D3), U22.5 (D3)
D5: J17.27, J18.27, J21.7, U1.28 (D5), U2.28 (D5), U3.22 (CD2), U4.23 (D5), U7.17 (DQ5), U8.17 (I/O5), U9.20 (D5), U15.19 (DQ5), U18.17 (D5), U21.4 (D2), U22.4 (D2)
D6: J17.25, J18.25, J21.5, U1.27 (D6), U2.27 (D6), U3.23 (CD1), U4.24 (D6), U7.18 (DQ6), U8.18 (I/O6), U9.21 (D6), U15.20 (DQ6), U18.18 (D6), U21.3 (D1), U22.3 (D1)
D7: J17.23, J18.23, J21.3, U1.26 (D7), U2.26 (D7), U3.24 (CD0), U4.25 (D7), U7.19 (DQ7), U8.19 (I/O7), U9.22 (D7), U15.21 (DQ7), U18.19 (D7), U21.2 (D0), U22.2 (D0)
DCD: J12.1, U10.16 (R2IN)
DCDIN: J4.3, U10.17 (R2OUT)
DSR: J12.6, U10.23 (R1IN)
DSRIN: U4.17 (DSRB), U10.22 (R1OUT)
DTR: J12.4, U10.24 (T1OUT)
DTROUT: U4.11 (DTRB), U10.19 (T1IN)
EXP2: J17.21, J18.21
EXP3: J17.19, J18.19
GND: BT1.2 (-), C1.1, C5.2, C6.2, C9.2, C10.2, C11.2, C12.2, C13.2, C14.2, C15.2, C16.2, C17.2, C18.2, C19.2, C20.2, C21.2, C22.2, C23.2, C24.2, C25.2, C26.2, C27.2, C28.2, C29.2, C30.2, C31.2, J2.1, J3.2, J4.1, J6.8, J6.SH (PAD), J7.1, J8.8, J8.SH (PAD), J9.2, J10.2, J11.1 (Ext), J12.5, J12.SH (PAD), J13.3, J14.1 (Ext), J15.2, J16.2, J16.3, J17.1, J17.40, J18.1, J18.40, J19.2, J21.1, J21.20, JP2.1 (A), R24.2, R26.2, SW70.2, TP2.1 (1_1), U1.21 (VSS), U2.1 (VSS), U3.12 (VSS), U4.1 (GND), U5.8 (GND), U6.11 (GND), U6.31 (GND), U7.14 (GND), U8.14 (GND), U9.14 (GND), U10.8 (GND), U11.7 (GND), U12.7 (GND), U13.7 (GND), U14.7 (GND), U15.16 (GND), U16.7 (GND), U17.7 (GND), U18.14 (GND), U18.21 (GND), U18.25 (VBAT), U19.8 (GND), U20.3 (A2)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
HRDB: J17.4, J17.6, J18.4, J18.6, R25.2, U11.1
IO1B: D2.1 (K), R29.1, SW69.16, U13.11, U13.12, U21.1 (OE)
IO2B: D3.1 (K), R30.1, SW69.15, U12.12, U12.13, U22.1 (OE)
IO3B: R31.1, SW69.14, U18.20 (~CE)
IO4B: J21.12, R32.1, SW69.13
IO5B: R33.1, SW69.12, U4.3 (CS1B)
IO6B: R34.1, SW69.11, U2.23 (CS2B)
IO7B: R35.1, SW69.10, U9.8 (~CS)
IO8B: R36.1, SW69.9, U20.2 (A1)
IRQB: D4.2 (A), J17.5, J18.5, R4.1, U1.4 (IRQB), U2.21 (IRQB), U4.26 (IRQB), U18.5 (IRQB)
LOADH: U13.4, U22.11 (Load)
LOADL: U13.1, U21.11 (Load)
NMIB: J17.7, J18.7, R3.1, U1.6 (NMIB), U6.21 (PD7)
unnamed: BT1.1 (+), R28.2, U18.26 (VBAUX)
unnamed: D1.1 (K), J20.2, R26.1
unnamed: D2.2 (A), D3.2 (A), R27.2, U15.22 (~CE)
unnamed: D4.1 (K), U3.16 (~INT)
unnamed: J2.2, U4.9 (CTSB)
unnamed: J3.1, SW70.1, U6.22 (PC0)
unnamed: J4.2, U4.16 (DCDB)
unnamed: J7.2, U9.23 (POTY)
unnamed: J7.3, U9.24 (POTX)
unnamed: C8.2, J11.2 (In), J14.2 (In), J15.1
unnamed: JP1.1 (A), U4.7 (XTALO), Y1.2
unnamed: JP1.2 (B), R38.2
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
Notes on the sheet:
ROM
Close JP1 & JP2 for WDC W65C51 or Rockwell R65C51P1/P2
RAM
IO4 / STORAGE
RAM / ROM
POWER
IO7 | SOUND
IO5 | SERIAL
IO8 | VIDEO
ROM DECODING
IO DECODING
IO 6 | GPIO
CART / EXP PORT
IO3 | RTC
CPU / CLOCK
IO 1&2 | EXTENDED RAM
KEYBOARD MATRIX

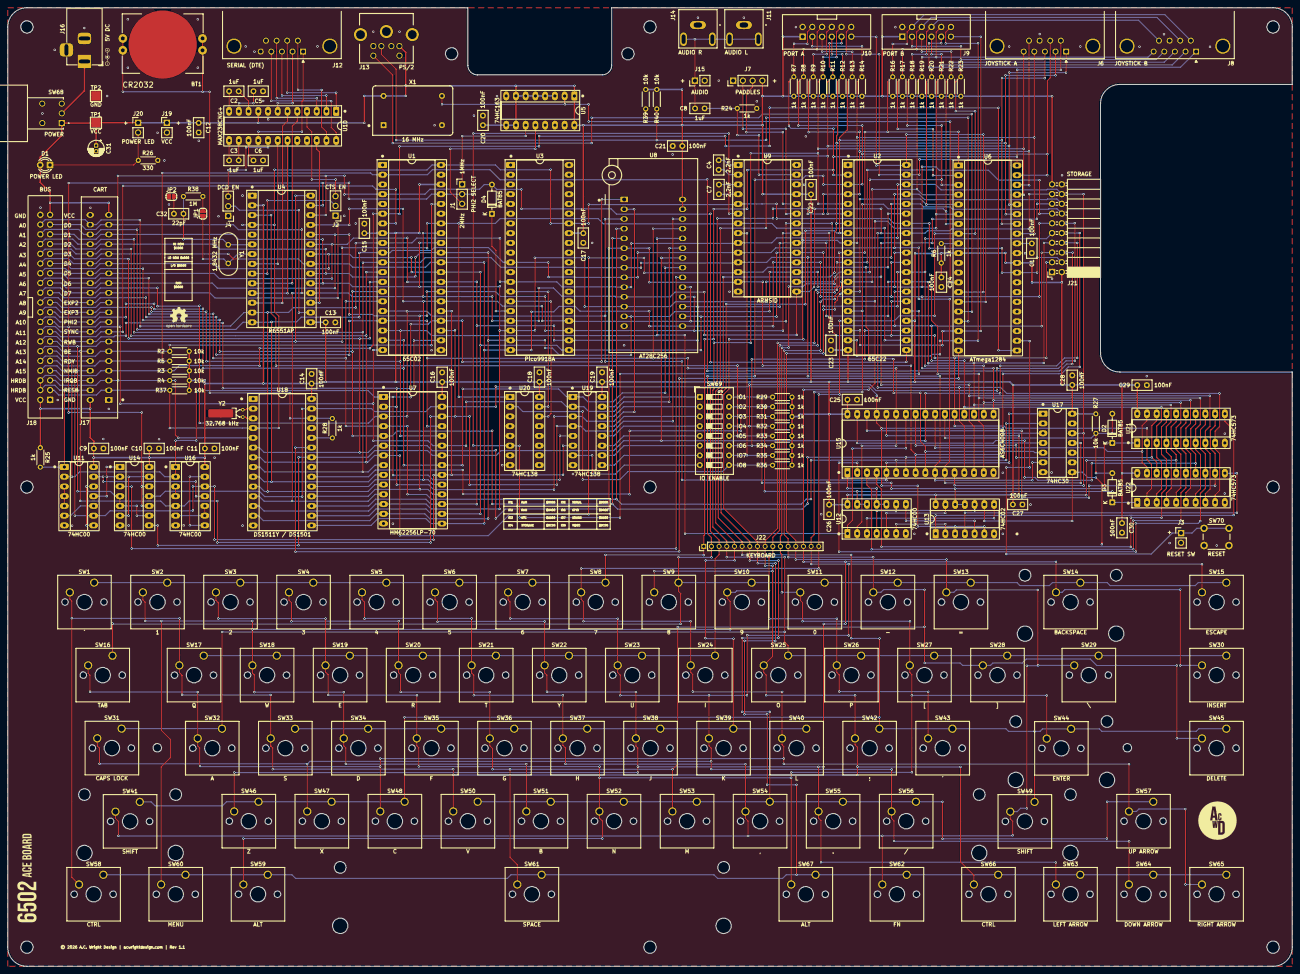
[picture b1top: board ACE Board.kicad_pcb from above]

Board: 2 copper layers, 335.0 x 250.0 mm, 207 parts (0 on the bottom side), 155 nets.

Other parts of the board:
CENTERPOS: Polarity_Center_Positive_6mm_SilkScreen
H1, H2, H2#2, H2#3, H2#4, H2#5, H2#6, H3#2, H4: MountingHole; MountingHole_3.2mm_M3
H3, H3#3: MountingHole; MountingHole_2.2mm_M2

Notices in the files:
README.md:
License:
Hardware designs are released under the [CERN Open Hardware Licence Version 2 – Permissive](https://ohwr.org/cern_ohl_p_v2.txt).
Firmware is released under the MIT License — [AB Controller](./Firmware/AB%20Controller/LICENSE) and [ASDA Controller](./Firmware/ASDA%20Controller/LICENSE).
Hardware/ACE Board/Rev 1.1/ACE Board.kicad_pcb:
© 2026 A.C. Wright Design | acwrightdesign.com | Rev 1.1
Hardware/ACE CF Adapter/Rev 1.0/ACE CF Adapter.kicad_pcb:
© 2026 A.C. Wright Design | acwrightdesign.com | Rev 1.0
